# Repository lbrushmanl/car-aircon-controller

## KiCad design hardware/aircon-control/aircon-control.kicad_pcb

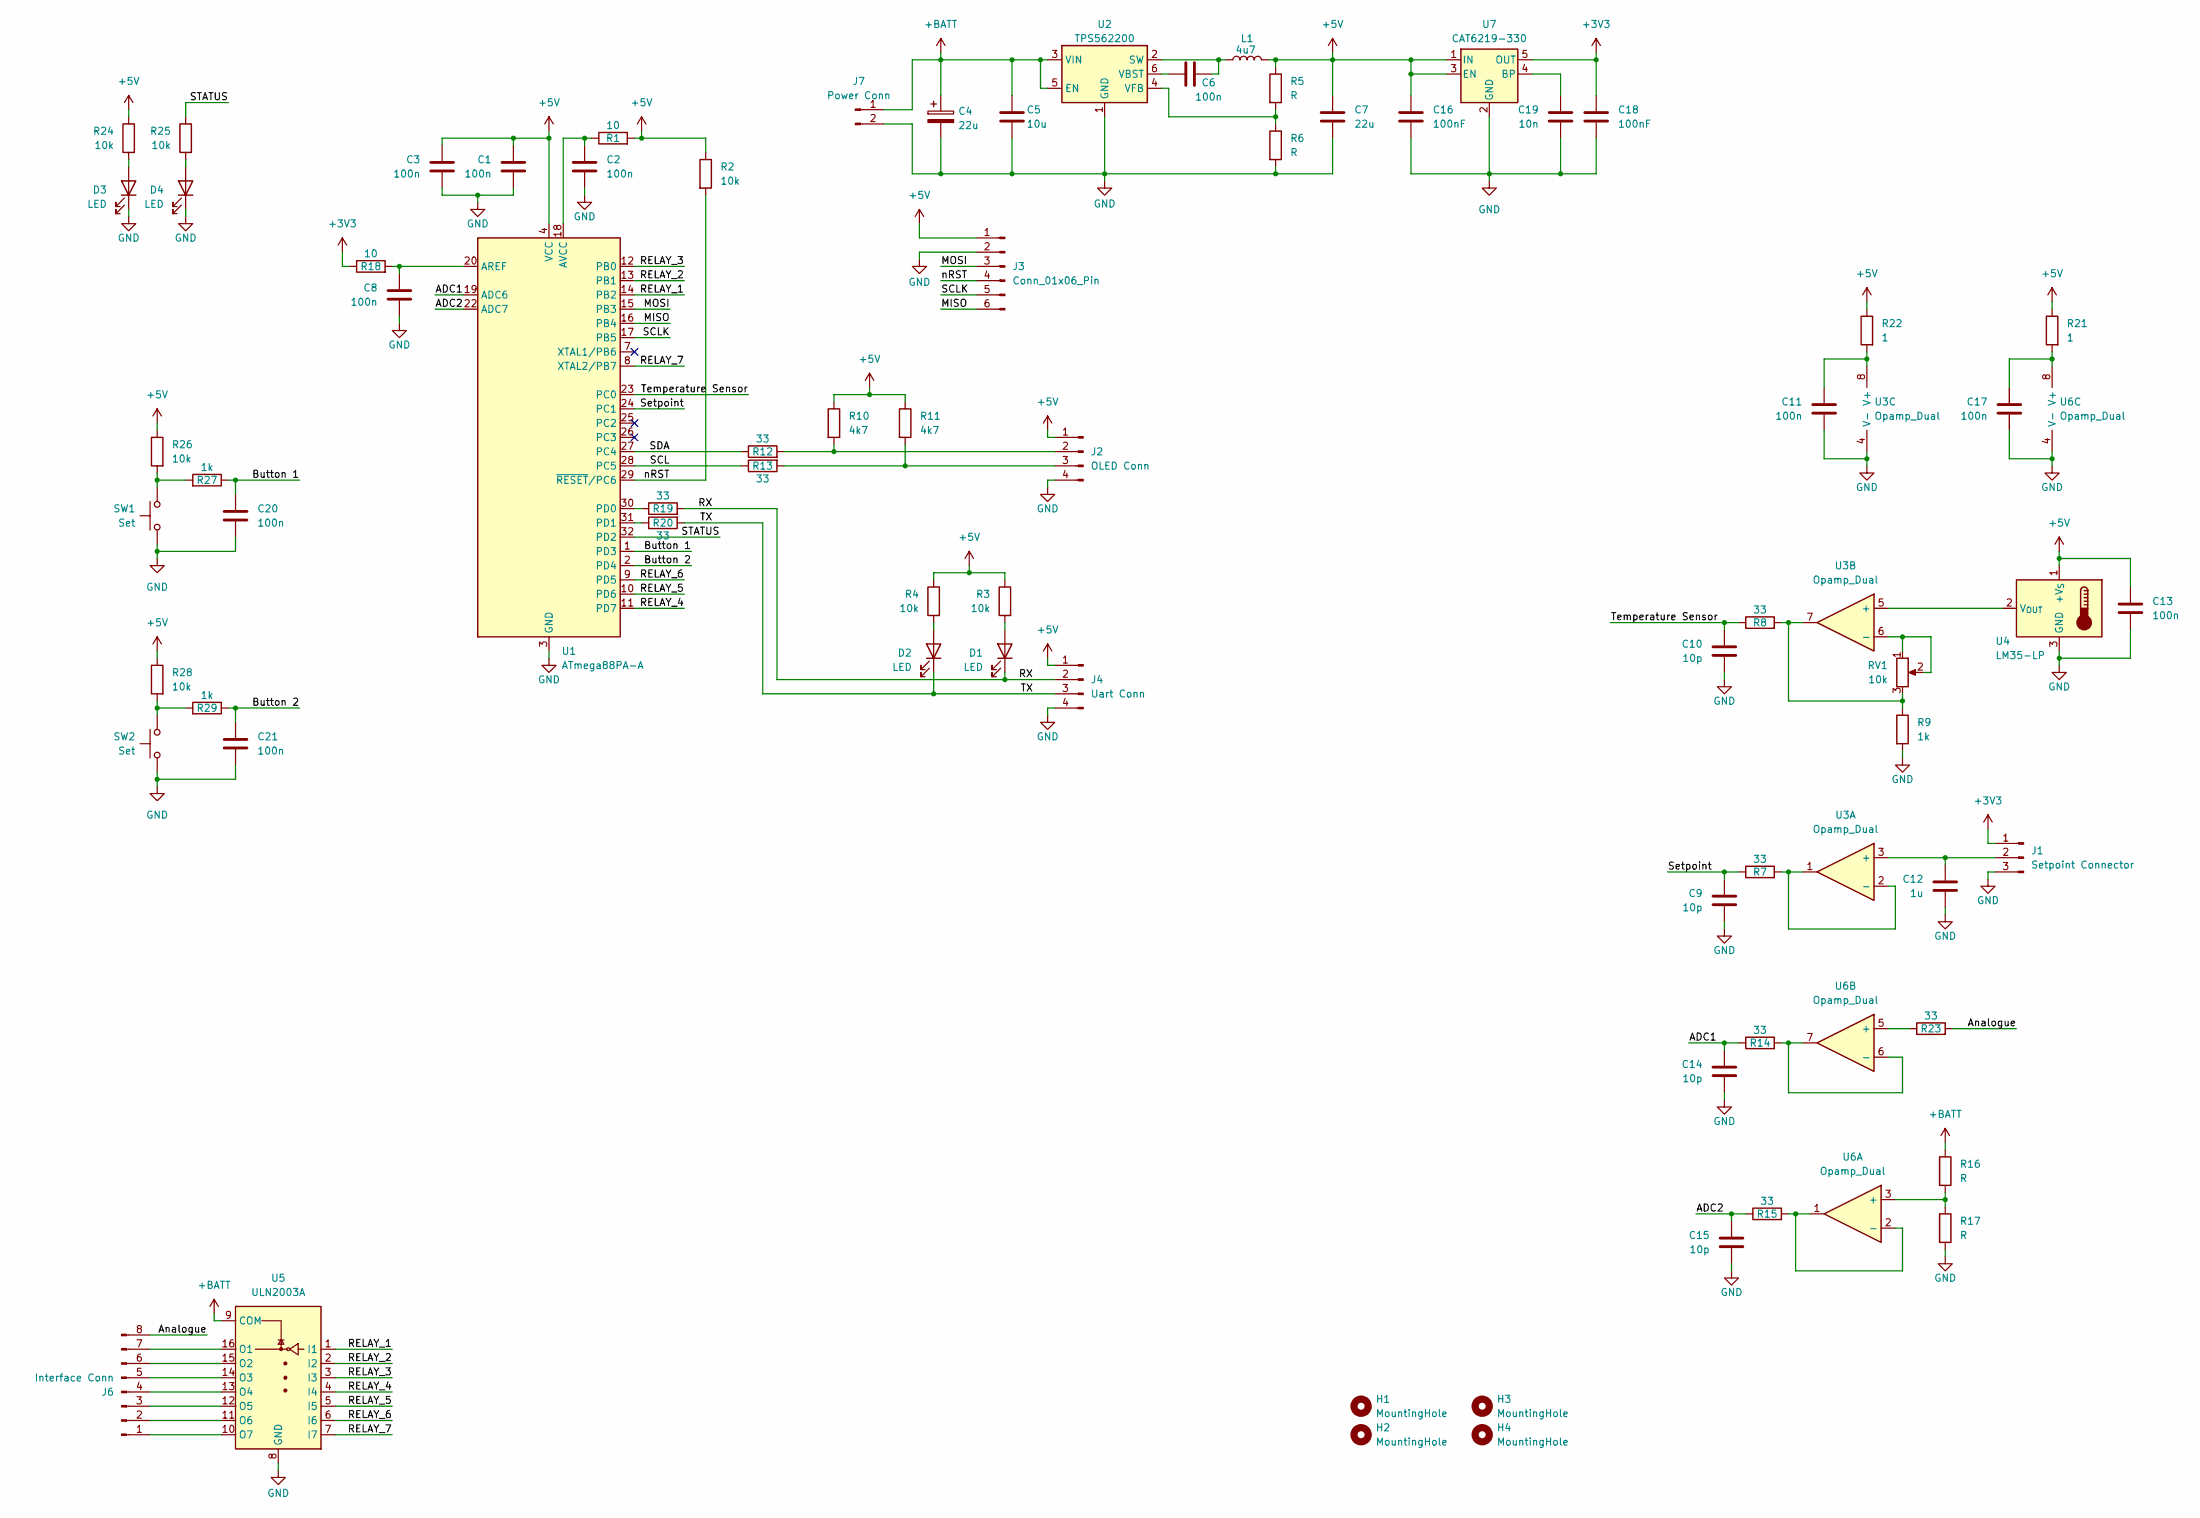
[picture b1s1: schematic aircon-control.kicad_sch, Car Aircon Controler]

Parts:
C1, C2, C3, C8, C11, C13, C17, C20, C21: 100n; C_0603_1608Metric
C4: 22u; CP_Radial_D5.0mm_P2.50mm
C5: 10u; C_1206_3216Metric
C6: 100n; C_0402_1005Metric
C7: 22u; C_1206_3216Metric
C9, C10, C14, C15: 10p; C_0603_1608Metric
C12: 1u; C_0603_1608Metric
C16, C18: 100nF; C_0603_1608Metric
C19: 10n; C_0603_1608Metric
D1, D2, D3, D4: LED; LED_0603_1608Metric
H1, H2, H3, H4: MountingHole; MountingHole_3.2mm_M3
J1: Setpoint Connector; Molex_KK-254_AE-6410-03A_1x03_P2.54mm_Vertical
J2: OLED Conn; PinHeader_1x04_P2.54mm_Vertical
J3: Conn_01x06_Pin; PinHeader_2x03_P2.54mm_Vertical
J4: Uart Conn; PinHeader_1x04_P2.54mm_Vertical
J6: Interface Conn; PhoenixContact_MC_1,5_8-G-3.81_1x08_P3.81mm_Horizontal
J7: Power Conn; PhoenixContact_MC_1,5_2-G-3.81_1x02_P3.81mm_Horizontal
L1: 4u7; L_1210_3225Metric
R1, R18: 10; R_0603_1608Metric
R2, R3, R4, R24, R25, R28: 10k; R_0603_1608Metric
R5, R6: R; R_0402_1005Metric
R7, R8, R12, R13, R14, R15, R19, R20: 33; R_0603_1608Metric
R9, R27, R29: 1k; R_0603_1608Metric
R10, R11: 4k7; R_0603_1608Metric
R16: R; R_1206_3216Metric
R17: R; R_0603_1608Metric
R21, R22: 1; R_0603_1608Metric
R23: 33; R_1206_3216Metric
R26: 10k; R_1206_3216Metric
RV1: 10k; Potentiometer_Bourns_3296W_Vertical
SW1, SW2: Set; SW_PUSH_6mm
U1: ATmega88PA-A; TQFP-32_7x7mm_P0.8mm
U2: TPS562200; SOT-23-6
U3, U6: Opamp_Dual; VSSOP-8_3x3mm_P0.65mm
U4: LM35-LP; TO-92_Wide
U5: ULN2003A; SOIC-16_3.9x9.9mm_P1.27mm
U7: CAT6219-330; SOT-23-5

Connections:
+3V3: C18.1, J1.1, R18.1, U7.5 (OUT)
+5V: C1.1, C3.1, C7.1, C13.1, C16.1, J2.1, J3.1, J4.1, L1.2, R1.2, R2.1, R3.1, R4.1, R5.1, R10.1, R11.1, R21.1, R22.1, R24.1, R26.1, R28.1, U1.4 (VCC), U1.6 (VCC), U4.1 (+V_{S}), U7.1 (IN), U7.3 (EN)
+BATT: C4.1, C5.1, J7.1, R16.1, U2.3 (VIN), U2.5 (EN), U5.9 (COM)
/ADC1: C14.1, R14.1, U1.19 (ADC6)
/ADC2: C15.1, R15.1, U1.22 (ADC7)
/Analogue: J6.8, R23.2
/Button 1: C20.1, R27.1, U1.1 (PD3)
/Button 2: C21.1, R29.1, U1.2 (PD4)
/MISO: J3.6, U1.16 (PB4)
/MOSI: J3.3, U1.15 (PB3)
/RELAY_1: U1.14 (PB2), U5.1 (I1)
/RELAY_2: U1.13 (PB1), U5.2 (I2)
/RELAY_3: U1.12 (PB0), U5.3 (I3)
/RELAY_4: U1.11 (PD7), U5.4 (I4)
/RELAY_5: U1.10 (PD6), U5.5 (I5)
/RELAY_6: U1.9 (PD5), U5.6 (I6)
/RELAY_7: U1.8 (XTAL2/PB7), U5.7 (I7)
/RX: D1.1 (K), J4.2, R19.2
/SCL: R13.1, U1.28 (PC5)
/SCLK: J3.5, U1.17 (PB5)
/SDA: R12.1, U1.27 (PC4)
/STATUS: R25.1, U1.32 (PD2)
/Setpoint: C9.1, R7.1, U1.24 (PC1)
/TX: D2.1 (K), J4.3, R20.2
/Temperature Sensor: C10.1, R8.1, U1.23 (PC0)
/nRST: J3.4, R2.2, U1.29 (~RESET/PC6)
GND: C1.2, C2.2, C3.2, C4.2, C5.2, C7.2, C8.2, C9.2, C10.2, C11.2, C12.2, C13.2, C14.2, C15.2, C16.2, C17.2, C18.2, C19.2, C20.2, C21.2, D3.1 (K), D4.1 (K), J1.3, J2.4, J3.2, J4.4, J7.2, R6.2, R9.2, R17.2, SW1.2, SW2.2, U1.3 (GND), U1.5 (GND), U1.21 (GND), U2.1 (GND), U3.4 (V-), U4.3 (GND), U5.8 (GND), U6.4 (V-), U7.2 (GND)
unnamed: D1.2 (A), R3.2
unnamed: D2.2 (A), R4.2
unnamed: D3.2 (A), R24.2
unnamed: D4.2 (A), R25.2
unnamed: C12.1, J1.2, U3.3 (+)
unnamed: J2.2, R10.2, R12.2
unnamed: J2.3, R11.2, R13.2
unnamed: J6.1, U5.10 (O7)
unnamed: J6.2, U5.11 (O6)
unnamed: J6.3, U5.12 (O5)
unnamed: J6.4, U5.13 (O4)
unnamed: J6.5, U5.14 (O3)
unnamed: J6.6, U5.15 (O2)
unnamed: J6.7, U5.16 (O1)
unnamed: R8.2, R9.1, RV1.3, U3.7
unnamed: R26.2, R27.2, SW1.1
unnamed: R28.2, R29.2, SW2.1
unnamed: C8.1, R18.2, U1.20 (AREF)
unnamed: C2.1, R1.1, U1.18 (AVCC)
unnamed: R19.1, U1.30 (PD0)
unnamed: R20.1, U1.31 (PD1)
unnamed: C6.2, L1.1, U2.2 (SW)
unnamed: C6.1, U2.6 (VBST)
unnamed: R5.2, R6.1, U2.4 (VFB)
unnamed: R7.2, U3.1, U3.2 (-)
unnamed: U3.5 (+), U4.2 (V_{OUT})
unnamed: RV1.1, RV1.2, U3.6 (-)
unnamed: C11.1, R22.2, U3.8 (V+)
unnamed: R16.2, R17.1, U6.3 (+)
unnamed: R15.2, U6.1, U6.2 (-)
unnamed: R23.1, U6.5 (+)
unnamed: R14.2, U6.6 (-), U6.7
unnamed: C17.1, R21.2, U6.8 (V+)
unnamed: C19.1, U7.4 (BP)

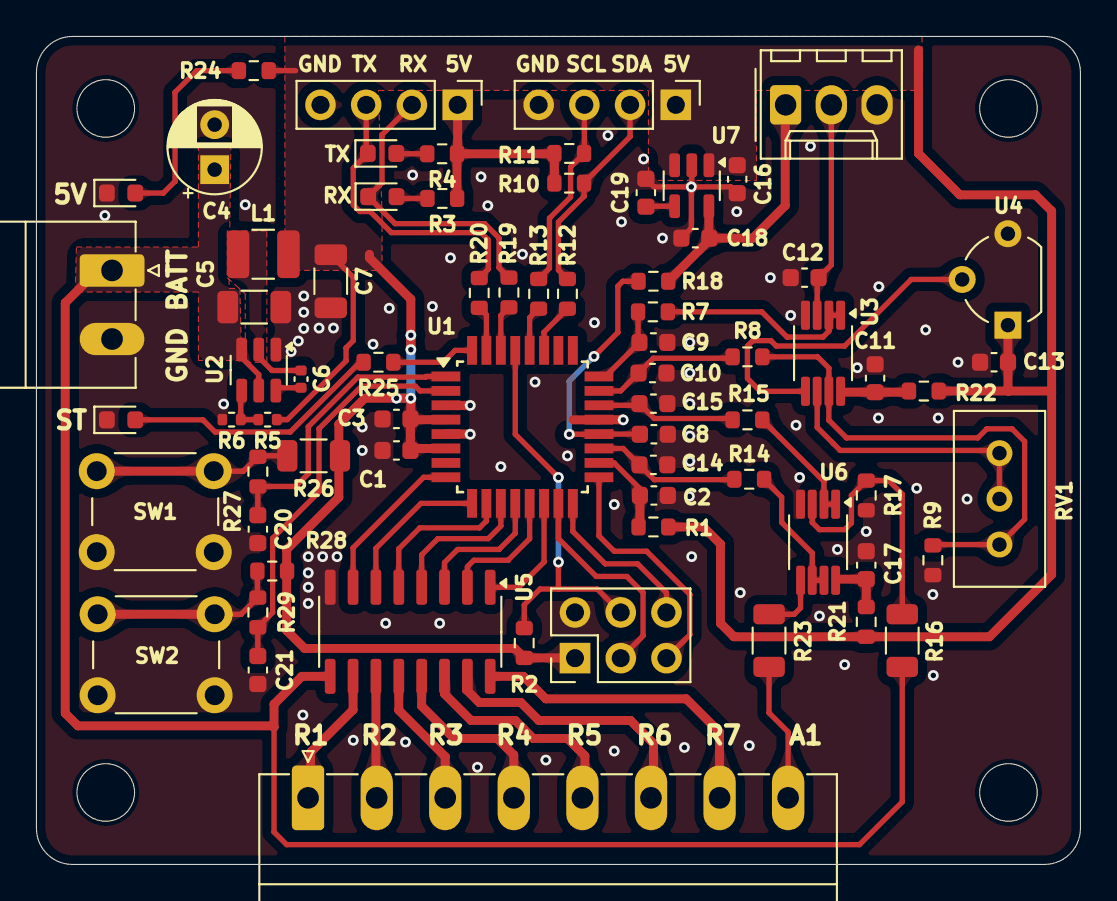
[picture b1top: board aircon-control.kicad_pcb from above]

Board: 2 copper layers, 58.0 x 46.0 mm, 75 parts (0 on the bottom side), 61 nets.

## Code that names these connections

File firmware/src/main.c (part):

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#define TO_Q8_VOLTAGE(sample)         (((int32_t) sample * FULL_SCALE_VOLTAGE_Q8) >> 10)

// Relay Mapping
// PB0 PB1 PB2 PB7 PD5 PD6 PD7
// 4   6   7   1   2   5   3
#define RELAY_1 _BV(PB7)
#define RELAY_2 _BV(PD5)
#define RELAY_3 _BV(PD7)
#define RELAY_4 _BV(PB0)
#define RELAY_5 _BV(PD6)
#define RELAY_6 _BV(PB1)
#define RELAY_7 _BV(PB2)

// Button Mapping
// PD3             PD4
// AIRCON_ENABLED  NEXT_SCREEN
#define AIRCON_ENABLED_BUTTON _BV(PD3)
#define NEXT_SCREEN_BUTTON    _BV(PD4)

// LED Mapping
// PD2
// Status
#define STATUS_LED _BV(PD2)


// ADC Mapping
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
static inline void relay_gpio_init(void)
{
    CONFIG_PIN(DDRB, RELAY_1 | RELAY_4 | RELAY_6 | RELAY_7);
    CONFIG_PIN(DDRD, RELAY_2 | RELAY_5 | RELAY_3);
}


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        // SET_OUTPUT_HIGH(PORTD, STATUS_LED);
        // for (int i = 0; i < 9; i++)
        // {
        //     TOGGLE_PIN(PORTC, PC5);
        //     _delay_us(10);
        // }

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
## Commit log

2026-03-14 First commit of project.
    Includeds working controller.
